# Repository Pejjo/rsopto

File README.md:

# rsopto
RS232 opto interface simplex

Simple interface to transmit serial data from a RS232 device over fibre optic wire. Airgap.

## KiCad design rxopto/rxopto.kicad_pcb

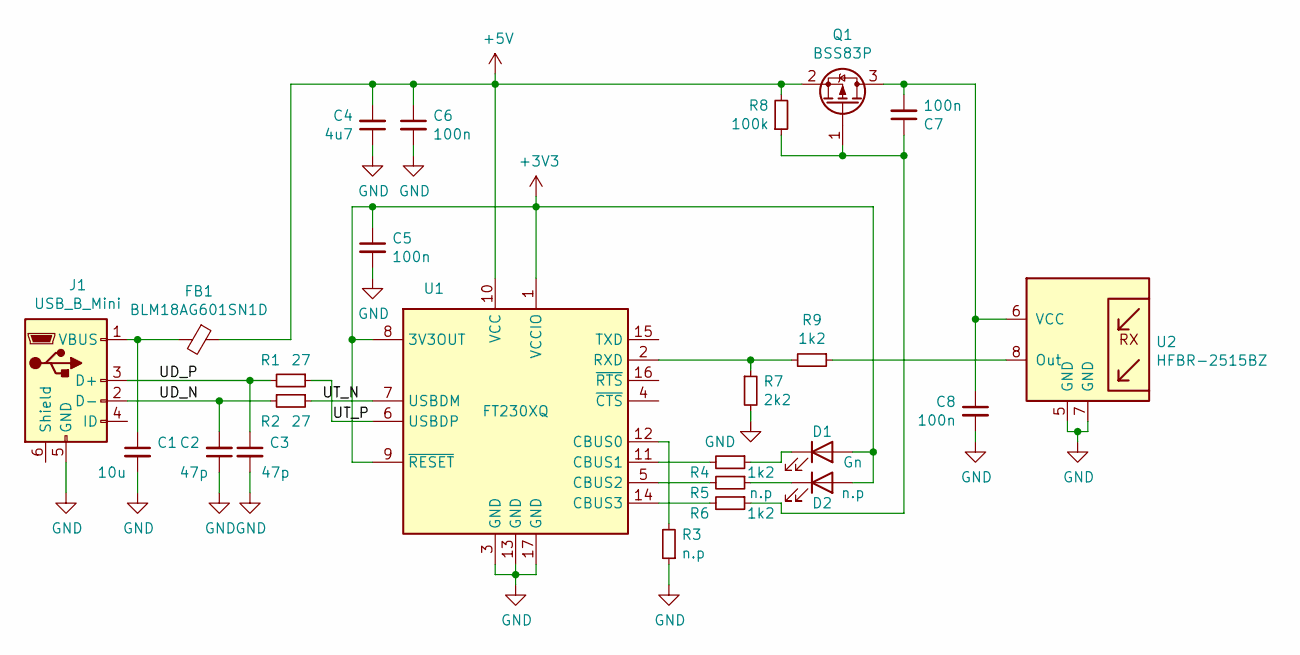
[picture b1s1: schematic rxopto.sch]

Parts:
C1: 10u; C_0805_2012Metric
C2, C3: 47p; C_0603_1608Metric
C4: 4u7; C_0805_2012Metric
C5, C6, C7, C8: 100n; C_0603_1608Metric
D1: Gn; D_0603_1608Metric
D2: n.p; D_0603_1608Metric
FB1: BLM18AG601SN1D; L_0603_1608Metric
J1: USB_B_Mini; USB_Mini-B_Wuerth_65100516121_Horizontal
Q1: BSS83P; SOT-23
R1, R2: 27; R_0603_1608Metric
R3, R5: n.p; R_0603_1608Metric
R4, R6, R9: 1k2; R_0603_1608Metric
R7: 2k2; R_0603_1608Metric
R8: 100k; R_0603_1608Metric
U1: FT230XQ; QFN-16-1EP_4x4mm_P0.65mm_EP2.1x2.1mm
U2: HFBR-2515BZ; HFBR-X515XZ

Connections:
+3V3: C5.1, D1.2 (A), D2.2 (A), U1.1 (VCCIO), U1.8 (3V3OUT), U1.9 (~RESET)
+5V: C4.2, C6.1, FB1.1, Q1.2 (S), R8.2, U1.10 (VCC)
/UD_N: C2.2, J1.2 (D-), R2.2
/UD_P: C3.1, J1.3 (D+), R1.2
/UT_N: R2.1, U1.7 (USBDM)
/UT_P: R1.1, U1.6 (USBDP)
GND: C1.2, C2.1, C3.2, C4.1, C5.2, C6.2, C8.2, J1.5 (GND), R3.1, R7.2, U1.3 (GND), U1.13 (GND), U1.17 (GND), U2.5 (GND), U2.7 (GND)
unnamed: C1.1, FB1.2, J1.1 (VBUS)
unnamed: C7.1, Q1.1 (G), R6.1, R8.1
unnamed: C7.2, C8.1, Q1.3 (D), U2.6 (VCC)
unnamed: D1.1 (K), R4.1
unnamed: D2.1 (K), R5.1
unnamed: R3.2, U1.12 (CBUS0)
unnamed: R4.2, U1.11 (CBUS1)
unnamed: R5.2, U1.5 (CBUS2)
unnamed: R6.2, U1.14 (CBUS3)
unnamed: R7.1, R9.2, U1.2 (RXD)
unnamed: R9.1, U2.8 (Out)

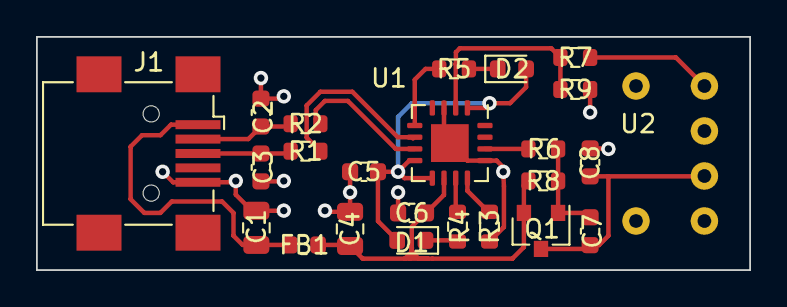
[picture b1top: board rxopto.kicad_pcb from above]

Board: 2 copper layers, 39.6 x 13.0 mm, 24 parts (0 on the bottom side), 18 nets.

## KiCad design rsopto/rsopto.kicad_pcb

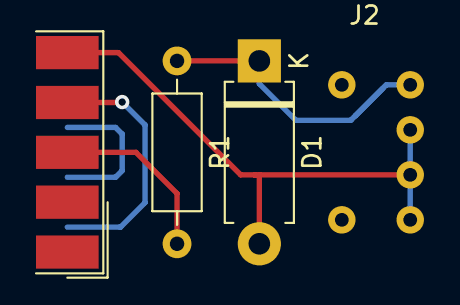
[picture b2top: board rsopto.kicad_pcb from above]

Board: 2 copper layers, 4 parts (0 on the bottom side), 5 nets.

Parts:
D1: 1N4148; D_DO-15_P10.16mm_Horizontal
J1: DB9_Female; DSUB-9_Female_EdgeMount_P2.77mm
J2: HFBR-1515BZ; HFBR-X515XZ
R1: 1k; R_Axial_DIN0207_L6.3mm_D2.5mm_P10.16mm_Horizontal

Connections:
GND: D1.2, J1.5, J2.5, J2.6, J2.7
unnamed: D1.1, J2.8, R1.1
unnamed: J1.3, R1.2
unnamed: J1.4, J1.6
unnamed: J1.7, J1.8

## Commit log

2021-03-15 Initial
2021-07-14 Fix structure
2021-07-14 Added rx
